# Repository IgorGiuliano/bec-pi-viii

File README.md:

# BEC - PROJETO INTEGRADOR VIII
Repositório para compartilhamento de infos/cod do projeto integrador 8
Pastas atuais:
- Hardware
- Firmware
  - Controller
- Backend
- Frontend

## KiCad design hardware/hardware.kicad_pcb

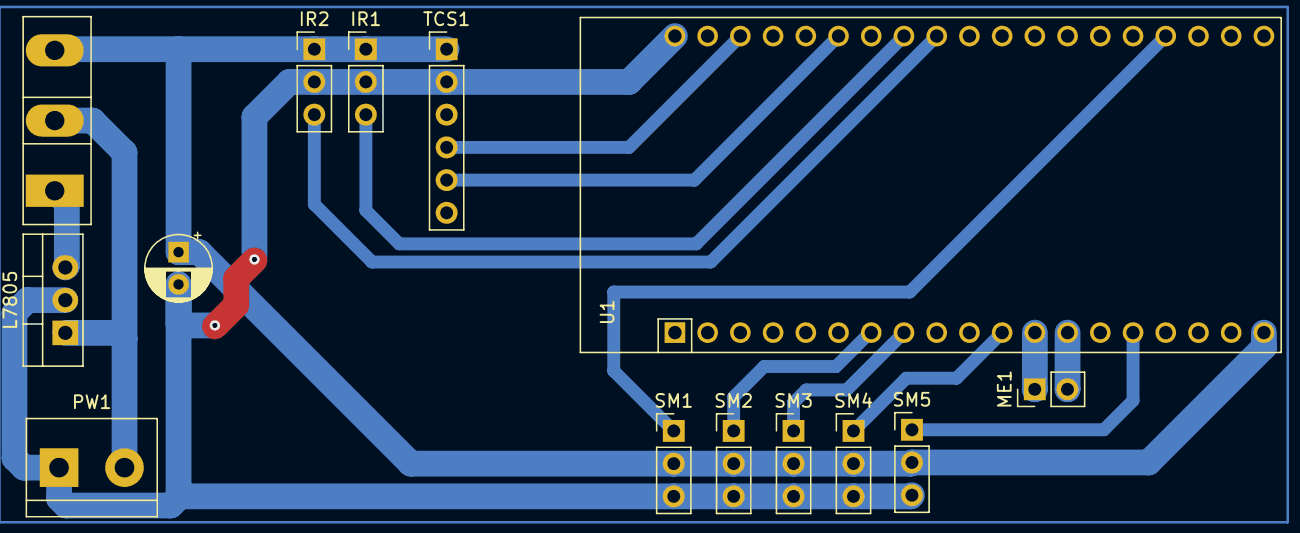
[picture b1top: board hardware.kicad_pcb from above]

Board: 2 copper layers, 14 parts (0 on the bottom side), 15 nets.

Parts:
C1: C_Polarized; CP_Radial_D5.0mm_P2.50mm
IR1, IR2: Conn_01x03_Pin; PinHeader_1x03_P2.54mm_Vertical
L7805: L7805; TO-220-3_Vertical
ME1: Conn_01x02_Pin; PinHeader_1x02_P2.54mm_Vertical
PW1: Screw_Terminal_01x02; TerminalBlock_bornier-2_P5.08mm
SM1, SM2, SM3, SM4, SM5: Conn_01x03_Pin; PinHeader_1x03_P2.54mm_Vertical
TCS1: Conn_01x06_Pin; PinHeader_1x06_P2.54mm_Vertical
TIP3055: TIP3055G; TO-247-3_Vertical
U1: ESP32-DEVKITC-32D

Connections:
unnamed: C1.1, IR1.1, IR2.1, SM1.2, SM2.2, SM3.2, SM4.2, SM5.2, TCS1.1, TIP3055.3 (E), U1.19
unnamed: C1.2, IR1.2, IR2.2, L7805.2 (GND), PW1.1, SM1.3, SM2.3, SM3.3, SM4.3, SM5.3, TCS1.2, U1.14, U1.20, U1.26
unnamed: IR1.3, U1.27
unnamed: IR2.3, U1.28
unnamed: L7805.1 (IN), PW1.2, TIP3055.2 (C)
unnamed: L7805.3 (OUT), TIP3055.1 (B)
unnamed: ME1.1, U1.12
unnamed: ME1.2, U1.13
unnamed: SM1.1, U1.35
unnamed: SM2.1, U1.7
unnamed: SM3.1, U1.8
unnamed: SM4.1, U1.11
unnamed: SM5.1, U1.15
unnamed: TCS1.4, U1.22
unnamed: TCS1.5, U1.25

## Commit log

2023-10-02 feat: inclusão do backend (e refactor das pastas de firmware)
2023-10-03 primeiro app
2023-10-04 packges modular/ provider/ screenutil
2023-10-04 teste
2023-10-05 modular
2023-10-17 feat: implementação das rotas de usuário em nestjs
2023-10-17 modular estruturado
2023-10-19 clean os
2023-10-19 MVC monitoring com erro
2023-10-23 feat: schema update for robotic arm and conveyor, env example
2023-10-23 monitoring page
2023-10-26 travar rotação
2023-10-26 notas drawer
2023-10-27 nome do app android
2023-10-27 icon app
2023-10-27 page monitoring
2023-10-27 titulo do app
2023-10-27 charts temp
2023-10-28 refactor: swagger tags in robotic-arm, user and conveyor
2023-10-28 feat: added dtos to robotic-arm and conveyor
2023-10-29 debugShowCheckedModeBanner
2023-10-29 feat: conveyor service
2023-10-29 feat: robotic arm service
2023-10-30 web view
2023-10-30 pading
2023-10-30 tamanho do grafico alterado
2023-10-30 auth dell
2023-10-30 transition
2023-10-31 icon web
2023-10-31 build web
2023-10-31 FlSpot
2023-11-01 title web
2023-11-01 title web test
2023-11-01 appbar color
2023-11-07 git ignore
2023-11-13 feat: hardware and backend (total/grouped_by_color, last twenty records)
2023-11-15 scroll web
2023-11-15 ajustes
2023-11-15 feat: hardware schematic
2023-11-15 refactor: hardware files
2023-11-15 feat: added footprints
2023-11-18 feat: pcb design
2023-11-25 feat: codigo do braco
2023-11-26 fix: robotic arm routes
2023-11-26 refactor: changed a4988
2023-11-26 feat: tá no nome né po
2023-11-26 fix: prisma import
2023-11-26 API https://api-robotinic.onrender.com/robotic-arm/count-day-records
2023-11-26 é isso
2023-11-26 fix: front pediu
2023-11-27 feat: Deus, eu creio
2023-11-27 umas alterações ai
2023-11-27 mudança de tipo
2023-11-27 del teste
2023-11-27 removendo código inutilizado
2023-11-28 mais
2023-11-28 fix: login
2023-11-28 feat: frontend web
2023-11-28 fix: route
2023-11-29 fix: Correcao do codigo do controle apos inclusao da rotina
2023-11-29 muita alteração
2023-11-29 feat: Adicionando servos restates para mapeamento do controle
2023-11-29 commits ai
2023-11-29 problems
2023-11-29 del build
2023-11-29 refactor: delete build files
2023-11-29 desc
2023-11-30 fix: codigo controle
2023-11-30 fix: mqtt
2023-12-01 feat: controller
2024-03-20 SvgImage e controller
